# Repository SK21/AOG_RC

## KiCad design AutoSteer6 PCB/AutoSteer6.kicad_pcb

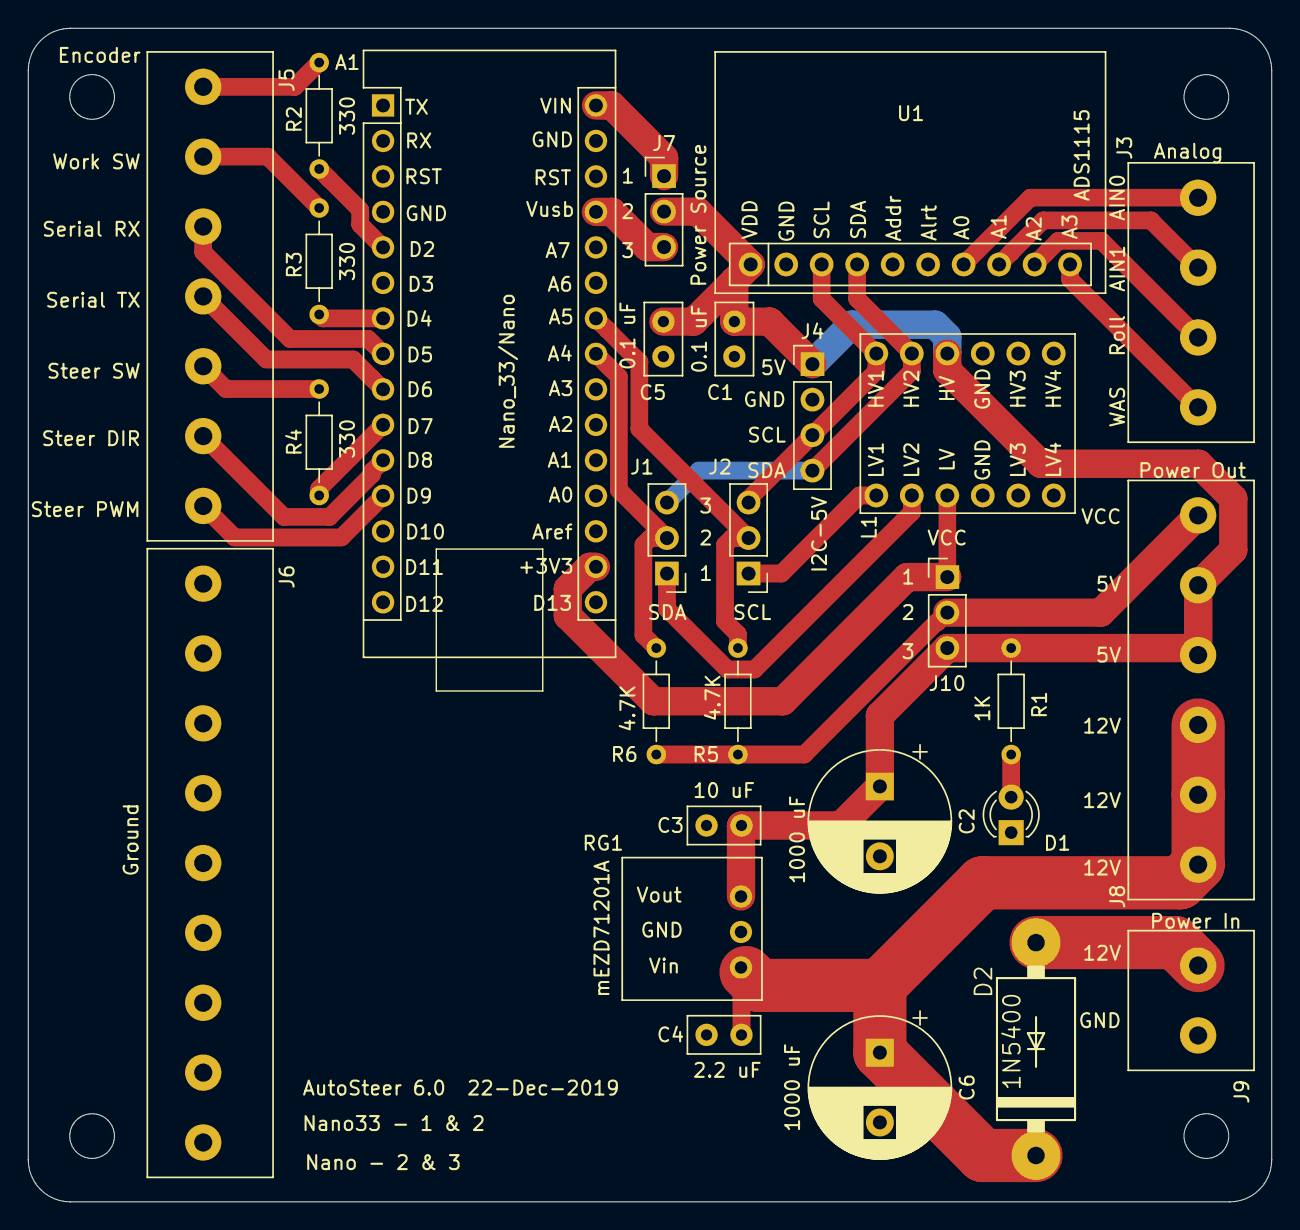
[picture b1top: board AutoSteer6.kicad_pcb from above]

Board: 2 copper layers, 89.0 x 84.0 mm, 28 parts (0 on the bottom side), 29 nets.

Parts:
A1: Nano_33/Nano; Nano_33
C1, C5: 0.1 uF; C_Disc_D5.0mm_W2.5mm_P2.50mm
C2, C6: 1000 uF; CP_Radial_D10.0mm_P5.00mm
C3: 10 uF; C_Disc_D5.0mm_W2.5mm_P2.50mm
C4: 2.2 uF; C_Disc_D5.0mm_W2.5mm_P2.50mm
D1: LED; LED_D3.0mm
D2: 1N5400
J1: SDA; PinHeader_1x03_P2.54mm_Vertical
J2: SCL; PinHeader_1x03_P2.54mm_Vertical
J3: Analog; Phoenix_4_pin_5mm_terminal_block
J4: I2C-5V; PinHeader_1x04_P2.54mm_Vertical
J5: GPIO's; Phoenix_7_pin_5mm_terminal_block
J6: Ground; Phoenix_9_pin_5mm_terminal_block
J7: Power Source; PinHeader_1x03_P2.54mm_Vertical
J8: Power Out; Phoenix_6_pin_5mm_terminal_block
J9: Power In; Phoenix_2_pin_5mm_terminal_block
J10: VCC; PinHeader_1x03_P2.54mm_Vertical
L1: LLC
R1: 1K; R_Axial_DIN0204_L3.6mm_D1.6mm_P7.62mm_Horizontal
R2, R3, R4: 330; R_Axial_DIN0204_L3.6mm_D1.6mm_P7.62mm_Horizontal
R5, R6: 4.7K; R_Axial_DIN0204_L3.6mm_D1.6mm_P7.62mm_Horizontal
RG1: mEZD71201A
U1: ADS1115; ads1115

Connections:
GND: A1.14, A1.19, C1.2, C2.2, C3.2, C4.2, C5.2, C6.2, D1.1, J4.2, J6.1, J6.2, J6.3, J6.4, J6.5, J6.6, J6.7, J6.8, J6.9, J9.1, L1.4, L1.10, RG1.2, U1.2, U1.5
unnamed: A1.2, J10.1, L1.3
unnamed: A1.8, J1.2, R6.2
unnamed: A1.9, J2.2, R5.2
unnamed: A1.12, J7.3
unnamed: A1.15, J7.1
unnamed: A1.20, R2.2
unnamed: A1.22, R3.2
unnamed: A1.23, J5.3
unnamed: A1.24, J5.4
unnamed: A1.25, R4.2
unnamed: A1.26, J5.6
unnamed: A1.27, J5.7
unnamed: C1.1, C2.1, C3.1, C5.1, J4.1, J7.2, J8.4, J8.5, J10.3, L1.9, R1.1, RG1.3, U1.1
unnamed: C4.1, C6.1, D2.C, J8.1, J8.2, J8.3, RG1.1
unnamed: D1.2, R1.2
unnamed: D2.A, J9.2
unnamed: J1.1, L1.2
unnamed: J1.3, J4.4, L1.8, U1.4
unnamed: J2.1, L1.1
unnamed: J2.3, J4.3, L1.7, U1.3
unnamed: J3.1, U1.10
unnamed: J3.2, U1.9
unnamed: J3.3, U1.8
unnamed: J3.4, U1.7
unnamed: J5.1, R2.1
unnamed: J5.2, R3.1
unnamed: J5.5, R4.1
unnamed: J8.6, J10.2, R5.1, R6.1

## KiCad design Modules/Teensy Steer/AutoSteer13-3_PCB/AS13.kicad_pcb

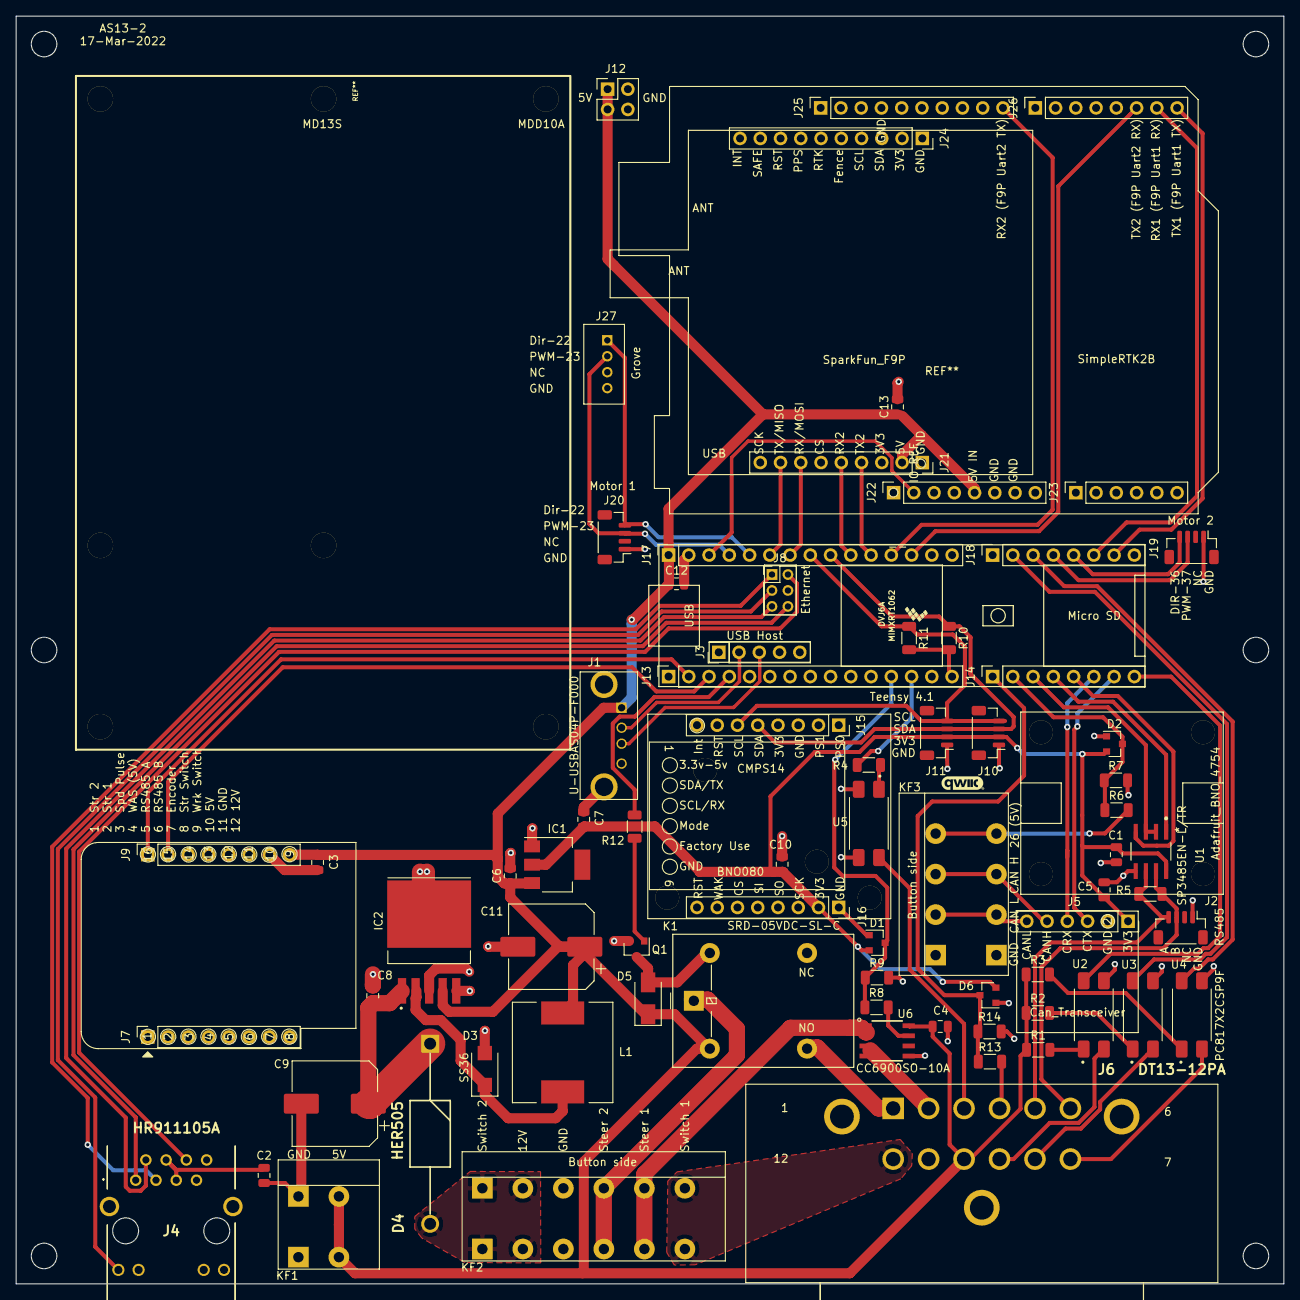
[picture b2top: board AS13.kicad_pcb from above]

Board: 2 copper layers, 159.0 x 159.0 mm, 82 parts (0 on the bottom side), 67 nets.

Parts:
  : MountingHole_3.2mm_M3
  #2,   #3,   #4,   #5,   #6: MountingHole_3.2mm_M3
--: Teensy 4.1; Teensy41_no_pins
C1, C2, C3, C4, C5, C10, C12, C13: 0.1uF; C_0805_2012Metric
C6: 10uF; C_0805_2012Metric
C7: 22uF; C_0805_2012Metric
C8: 1uF; C_0805_2012Metric
C9: 470uF; CP_Elec_10x10.5
C11: 330uF; CP_Elec_10x10.5
D1, D2, D6: BAV99; SOT-23
D3: SS36; SMA(DO-214AC)
D4: HER505; 1N5408
D5: 1N4007; D_SMA
IC1: AZ1117; SOT-223
IC2: XL2596; TO263-5L
J1: U-USBAS04P-F000
J2: RS485; Qwic_vertical
J3: Teensy_USBhost; PinHeader_1x05_P2.54mm_Vertical
J4: HR911105A
J5: PM254V-11-06-H85; PinSocket_1x06_P2.54mm_Vertical
J6: DT13-12PA; DT1312PA
J7: WemosD1_left; PinSocket_1x08_P2.54mm_Vertical
J8: Teensy_Ethernet; PinHeader_2x03_P2.00mm_Vertical
J9: WemosD1_right; PinSocket_1x08_P2.54mm_Vertical
J10, J11: I2C-3V3; Qwic_vertical
J12: Conn_02x02_Counter_Clockwise; PinSocket_2x02_P2.54mm_Vertical
J13, J17: Conn_01x15_Female; PinSocket_1x15_P2.54mm_Vertical
J14, J18: Conn_01x08_Female; PinSocket_1x08_P2.54mm_Vertical
J15: BNO080_left; PinSocket_1x08_P2.54mm_Vertical
J16: BNO080_right; PinSocket_1x08_P2.54mm_Vertical
J19: Motor 2; Qwic_vertical
J20: Motor 1; Qwic_vertical
J21: SF_F9P_left; PinSocket_1x09_P2.54mm_Vertical
J22: ArduSimple_tl; PinSocket_1x08_P2.54mm_Vertical
J23: ArduSimple_bl; PinSocket_1x06_P2.54mm_Vertical
J24: SF_F9P_right; PinSocket_1x10_P2.54mm_Vertical
J25: ArduSimple_tr; PinSocket_1x10_P2.54mm_Vertical
J26: ArduSimple_br; PinSocket_1x08_P2.54mm_Vertical
J27: Grove
K1: SRD-05VDC-SL-C; Songle_SRD-05VDC-SL-C
KF1: KF142V-5.0-2P; KF142V-5.08-2P
KF2: KF142V-5.0-6P; KF142V-5.08-6P
KF3: KF142V-5.0-4P; KF142V-5.08-4P
L1: SMDRI127-330MT; TMPA1265SP-101MN-D
M1: CMPS14; CMPS14_no_pins
Q1: BC847; SOT-23
R1, R2, R3: 200; R_1206_3216Metric
R4: 100; R_1206_3216Metric
R5: 120; R_1206_3216Metric
R6, R8, R12, R13: 1K; R_1206_3216Metric
R7, R9, R14: 2K; R_1206_3216Metric
R10, R11: 2.2K; R_1206_3216Metric
U1: SP3485EN-L/TR; Maxim_Integrated-S8-2-0-P-MFG
U2, U3, U4, U5: PC817X2CSP9F; SOIC254P960X420-4N
U6: CC6900SO-10A; SOIC127P600X175-8N

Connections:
GND: C1.2, C2.2, C3.2, C4.2, C5.2, C6.2, C7.2, C8.2, C9.2, C10.2, C11.2, C12.2, C13.2, D1.1, D2.1, D3.2, D6.1, IC1.1, IC2.3, IC2.5, IC2.6, J1.4, J1.5, J1.6, J2.1, J3.4, J3.5, J4.8, J4.10, J4.MH1, J4.MH2, J5.2, J6.11, J8.4, J9.7, J10.1, J11.1, J12.3, J12.4, J13.1, J16.1, J17.2, J17.15, J19.1, J20.1, J21.1, J22.6, J22.7, J25.4, J27.4, KF1.1, KF2.3, KF3.1, Q1.2, R7.2, R9.2, R14.2, U1.5, U2.3, U3.3, U4.3, U5.2, U5.3, U6.5
unnamed: C1.1, C5.1, C7.1, C10.1, D1.2, D2.2, D6.2, IC1.2, J5.1, J10.2, J11.2, J16.2, U1.8
unnamed: C2.1, J4.4, J4.5
unnamed: C8.1, C9.1, D4.1, IC2.1
unnamed: C3.1, C4.1, C6.1, C11.1, C12.1, C13.1, D5.1, IC1.3, IC2.4, J1.1, J6.10, J9.8, J12.1, J12.2, J17.1, J21.2, J22.5, K1.1, KF1.2, L1.2, R1.1, R2.1, R3.1, U6.8
unnamed: D1.3, J13.12, R8.1, R9.1
unnamed: D2.3, J14.2, R6.1, R7.1
unnamed: D3.1, IC2.2, L1.1
unnamed: D4.2, KF2.1, KF2.2
unnamed: D5.2, K1.2, Q1.3
unnamed: D6.3, J14.1, R13.1, R14.1
unnamed: J1.2, J3.2
unnamed: J1.3, J3.3
unnamed: J2.3, J6.6, R5.1, U1.7
unnamed: J2.4, J6.5, R5.2, U1.6
unnamed: J4.1, J8.6
unnamed: J4.2, J8.5
unnamed: J4.3, J8.1
unnamed: J4.6, J8.2
unnamed: J4.9, J8.3
unnamed: J5.5, KF3.3
unnamed: J5.6, KF3.2
unnamed: J6.1, K1.5
unnamed: J6.2, U6.3, U6.4
unnamed: J6.3, U5.4
unnamed: J6.4, R13.2
unnamed: J6.7, U4.2
unnamed: J6.8, U3.2
unnamed: J6.9, U2.2
unnamed: J6.12, KF2.6
unnamed: J10.3, J11.3, J15.5, J17.9, R10.1
unnamed: J10.4, J11.4, J15.6, J17.8, R11.1
unnamed: J9.1, J13.2
unnamed: J9.2, J13.3
unnamed: J13.4, R12.2
unnamed: J13.13, R4.1
unnamed: J13.15, R10.2, R11.2
unnamed: J14.3, U1.2, U1.3
unnamed: J14.4, U1.1
unnamed: J14.5, U1.4
unnamed: J5.4, J14.6
unnamed: J5.3, J14.7
unnamed: J14.8, U2.4
unnamed: J17.3, J22.2
unnamed: J17.4, J20.3, J27.2
unnamed: J17.5, J20.4, J27.1
unnamed: J17.6, J21.8
unnamed: J17.7, J21.7
unnamed: J17.10, J21.5
unnamed: J17.11, J21.4
unnamed: J17.12, J25.10
unnamed: J17.13, J26.6
unnamed: J18.2, U3.4
unnamed: J18.3, U4.4
unnamed: J18.4, J19.3
unnamed: J18.5, J19.4
unnamed: J18.6, J26.7
unnamed: J18.7, J26.8
unnamed: K1.3, KF2.4
unnamed: KF2.5, U6.1, U6.2
unnamed: KF3.4, R6.2
unnamed: Q1.1, R12.1
unnamed: R1.2, U2.1
unnamed: R2.2, U3.1
unnamed: R3.2, U4.1
unnamed: R4.2, U5.1
unnamed: R8.2, U6.7

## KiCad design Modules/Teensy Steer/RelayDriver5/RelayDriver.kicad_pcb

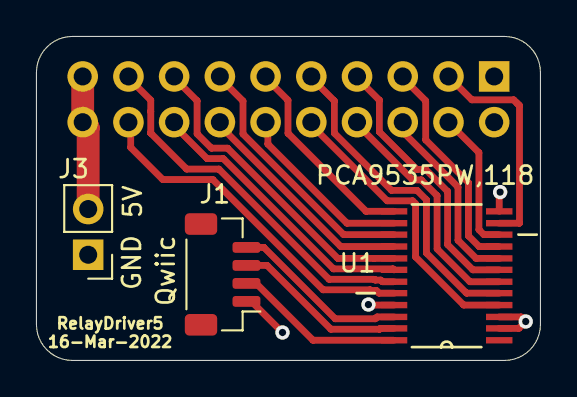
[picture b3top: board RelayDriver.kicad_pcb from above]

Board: 2 copper layers, 28.0 x 18.0 mm, 4 parts (1 on the bottom side), 21 nets.

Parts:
J1: Qwiic; Qwic_vertical
J2: PinSocket_2x10_P2.54mm_Vertical
J3: PinHeader_1x02_P2.54mm_Vertical
U1: PCA9535PW,118; SOP65P640X110-24N

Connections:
GND: J1.1, J2.1, J2.2, J3.1, U1.2, U1.3, U1.12, U1.21
unnamed: J1.2, U1.24
unnamed: J1.3, U1.23
unnamed: J1.4, U1.22
unnamed: J2.3, U1.11
unnamed: J2.4, U1.10
unnamed: J2.5, U1.9
unnamed: J2.6, U1.8
unnamed: J2.7, U1.7
unnamed: J2.8, U1.6
unnamed: J2.9, U1.5
unnamed: J2.10, U1.4
unnamed: J2.11, U1.13
unnamed: J2.12, U1.14
unnamed: J2.13, U1.15
unnamed: J2.14, U1.16
unnamed: J2.15, U1.17
unnamed: J2.16, U1.18
unnamed: J2.17, U1.19
unnamed: J2.18, U1.20
unnamed: J2.19, J2.20, J3.2

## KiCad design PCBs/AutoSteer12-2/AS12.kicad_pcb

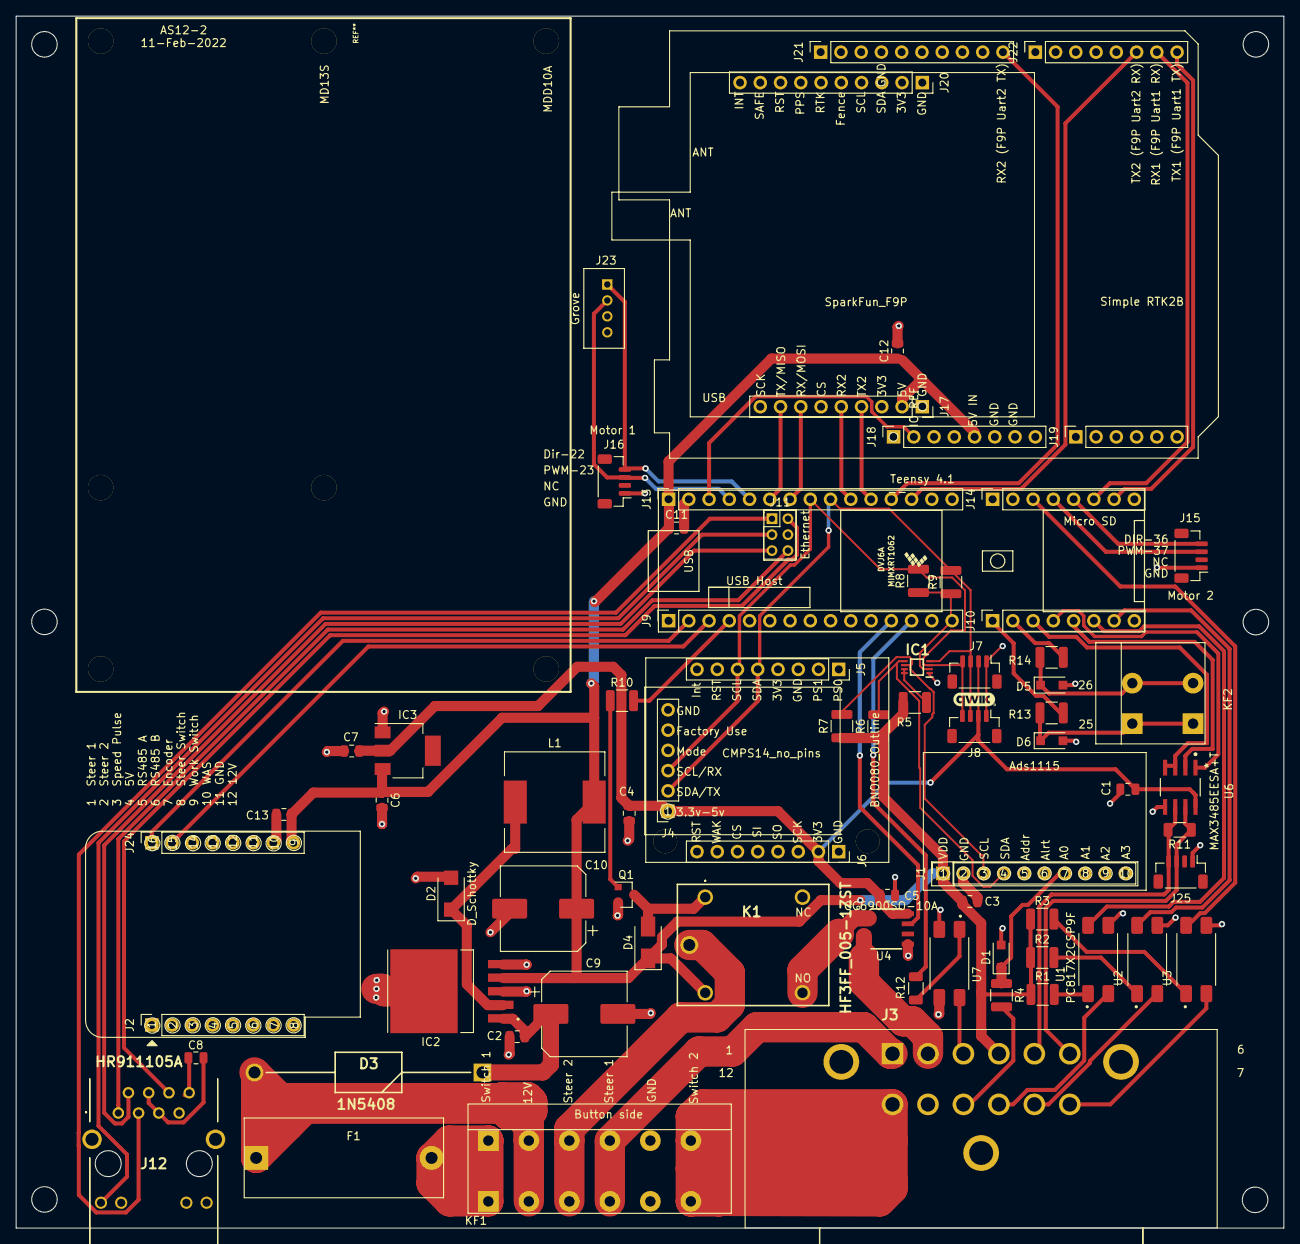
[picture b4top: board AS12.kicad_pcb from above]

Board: 2 copper layers, 159.0 x 152.0 mm, 81 parts (0 on the bottom side), 66 nets.

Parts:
 : MountingHole_3.2mm_M3
 #2,  #3,  #4,  #5,  #6: MountingHole_3.2mm_M3
--: Teensy 4.1; Teensy41_no_pins
C1, C3, C4, C5, C8, C11, C12, C13: 0.1uF; C_0805_2012Metric
C2: CL21B105KAFNNNE; C_0805_2012Metric
C6: 10uF; C_0805_2012Metric
C7: 22uF; C_0805_2012Metric
C9: RVT1V471M1010; CP_Elec_10x10.5
C10: RVT1V331M1010; CP_Elec_10x10.5
D1, D5, D6: Zener Diode; D_SOD-123F
D2: D_Schottky; SMA(DO-214AC)
D3: 1N5408; DO-201AD-28
D4: 1N4007; D_SMA
F1: Fuse; Fuse_Holder_C3131
IC1: PCA9306DCUR; SOP50P310X90-8N
IC2: XL2596; TO263-5L
IC3: AZ1117; SOT-223
J1: ADS1115; PinSocket_1x10_P2.54mm_Vertical
J2: WemosD1_left; PinSocket_1x08_P2.54mm_Vertical
J3: DT13-12PA; DT1312PA
J4: CMPS14; PinSocket_1x06_P2.54mm_Vertical
J5: BNO080_left; PinSocket_1x08_P2.54mm_Vertical
J6: BNO080_right; PinSocket_1x08_P2.54mm_Vertical
J7, J8: I2C-3V3; Qwic_vertical
J9, J13: Conn_01x15_Female; PinSocket_1x15_P2.54mm_Vertical
J10, J14: Conn_01x08_Female; PinSocket_1x08_P2.54mm_Vertical
J11: Teensy_Ethernet; PinHeader_2x03_P2.00mm_Vertical
J12: HR911105A
J15: Motor 2; Qwic_vertical
J16: Motor 1; Qwic_vertical
J17: SF_F9P_left; PinSocket_1x09_P2.54mm_Vertical
J18: ArduSimple_tl; PinSocket_1x08_P2.54mm_Vertical
J19: ArduSimple_bl; PinSocket_1x06_P2.54mm_Vertical
J20: SF_F9P_right; PinSocket_1x10_P2.54mm_Vertical
J21: ArduSimple_tr; PinSocket_1x10_P2.54mm_Vertical
J22: ArduSimple_br; PinSocket_1x08_P2.54mm_Vertical
J23: Grove
J24: WemosD1_right; PinSocket_1x08_P2.54mm_Vertical
J25: RS485; Qwic_vertical
K1: HF3FF_005-1ZST; HF3FF0121ZST
KF1: KF142V-5.0-6P; KF142V-5.08-6P
KF2: KF142V-5.0-2P; KF142V-5.08-2P
L1: SMDRI127-330MT; TMPA1265SP-101MN-D
M1: CMPS14_no_pins
Q1: BC847; SOT-23
R1, R2, R3, R4, R13, R14: 200; R_1210_3225Metric
R5: 200K; R_1210_3225Metric
R6, R7: 341; R_1210_3225Metric
R8, R9: 217; R_1210_3225Metric
R10: 1K; R_1210_3225Metric
R11: 120; R_1206_3216Metric
R12: 100; R_1206_3216Metric
U1, U2, U3, U7: PC817X2CSP9F; SOIC254P960X420-4N
U4: CC6900SO-10A; SOIC127P600X175-8N
U6: MAX3485EESA+T; Maxim_Integrated-S8-2-0-P-MFG

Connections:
GND: C1.2, C2.2, C3.2, C4.2, C5.2, C6.2, C7.2, C8.2, C9.2, C10.2, C11.2, C12.2, C13.2, D1.2, D2.2, D5.2, D6.2, IC1.1, IC2.3, IC2.5, IC2.6, IC3.1, J1.2, J1.5, J3.11, J4.6, J6.1, J7.1, J8.1, J9.1, J11.4, J12.8, J12.10, J13.2, J13.15, J15.1, J16.1, J17.1, J18.6, J18.7, J21.4, J23.4, J24.7, J25.1, KF1.5, Q1.2, U1.3, U2.3, U3.3, U4.5, U6.5, U7.2, U7.3
unnamed: C1.1, C4.1, C5.1, C7.1, IC3.2, J4.1, J6.2, J7.2, J8.2, U4.8, U6.8
unnamed: C2.1, C9.1, D3.1, IC2.1
unnamed: C8.1, J12.4, J12.5
unnamed: C3.1, C6.1, C10.1, C11.1, C12.1, C13.1, D4.1, IC2.4, IC3.3, J1.1, J3.4, J13.1, J17.2, J18.5, J24.8, K1.3, L1.2, R1.1, R2.1, R3.1, R5.1, R6.1, R7.1
unnamed: D1.1, J1.7, R4.1
unnamed: D2.1, IC2.2, L1.1
unnamed: D3.2, F1.1, KF1.2
unnamed: D4.2, K1.1, Q1.3
unnamed: D5.1, KF2.2, R14.1
unnamed: D6.1, KF2.1, R13.1
unnamed: F1.2, KF1.1
unnamed: IC1.2, J9.15, R8.1, R9.1
unnamed: IC1.3, J4.3, J5.6, J7.4, J8.4, J13.8, R8.2
unnamed: IC1.4, J4.2, J5.5, J7.3, J8.3, J13.9, R9.2
unnamed: IC1.5, J1.4, R6.2
unnamed: IC1.6, J1.3, R7.2
unnamed: IC1.7, IC1.8, R5.2
unnamed: J3.1, KF1.4
unnamed: J3.2, U4.3, U4.4
unnamed: J3.3, U7.4
unnamed: J3.7, U3.2
unnamed: J3.8, U2.2
unnamed: J3.9, U1.2
unnamed: J3.10, R4.2
unnamed: J3.12, KF1.6
unnamed: J9.4, R10.2
unnamed: J9.12, U4.7
unnamed: J9.13, R12.1
unnamed: J10.1, R13.2
unnamed: J10.2, R14.2
unnamed: J10.3, U6.3, U6.4
unnamed: J10.4, U6.1
unnamed: J10.5, U6.2
unnamed: J10.6, U1.4
unnamed: J10.7, U2.4
unnamed: J11.1, J12.3
unnamed: J11.2, J12.6
unnamed: J11.3, J12.9
unnamed: J11.5, J12.2
unnamed: J11.6, J12.1
unnamed: J13.3, J18.2
unnamed: J13.4, J16.3, J23.2
unnamed: J13.5, J16.4, J23.1
unnamed: J13.6, J17.8
unnamed: J13.7, J17.7
unnamed: J13.10, J17.5
unnamed: J13.11, J17.4
unnamed: J13.12, J21.10
unnamed: J13.13, J22.6
unnamed: J14.3, U3.4
unnamed: J14.4, J15.3
unnamed: J14.5, J15.4
unnamed: J14.6, J22.7
unnamed: J14.7, J22.8
unnamed: J9.2, J24.1
unnamed: J9.3, J24.2
unnamed: J3.6, J25.3, R11.1, U6.7
unnamed: J3.5, J25.4, R11.2, U6.6
unnamed: K1.2, KF1.3
unnamed: K1.4, U4.1, U4.2
unnamed: Q1.1, R10.1
unnamed: R1.2, U1.1
unnamed: R2.2, U2.1
unnamed: R3.2, U3.1
unnamed: R12.2, U7.1

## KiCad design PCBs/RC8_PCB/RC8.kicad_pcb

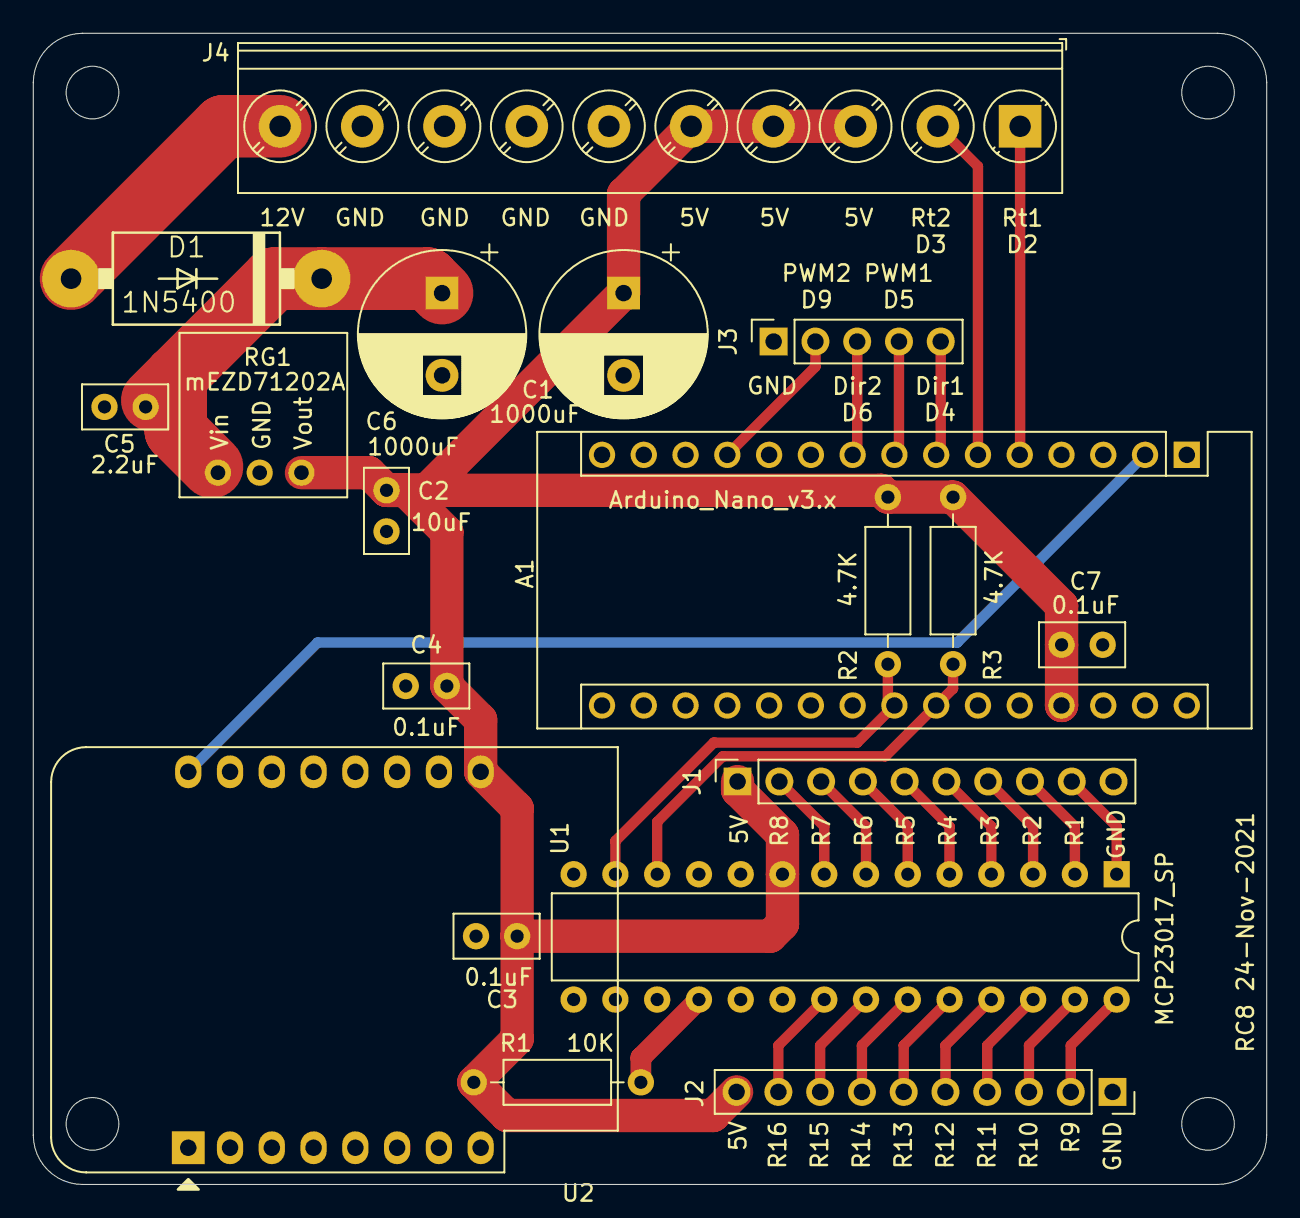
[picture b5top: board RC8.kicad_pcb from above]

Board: 2 copper layers, 75.0 x 70.0 mm, 23 parts (0 on the bottom side), 30 nets.

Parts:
 : MountingHole_3.2mm_M3
 #2,  #3,  #4: MountingHole_3.2mm_M3
A1: Arduino_Nano_v3.x; Arduino_Nano
C1, C6: 1000uF; CP_Radial_D10.0mm_P5.00mm
C2: 10uF; C_Disc_D5.0mm_W2.5mm_P2.50mm
C3, C4, C7: 0.1uF; C_Disc_D5.0mm_W2.5mm_P2.50mm
C5: 2.2uF; C_Disc_D5.0mm_W2.5mm_P2.50mm
D1: 1N5400
J1, J2: Conn_01x10_Female; PinSocket_1x10_P2.54mm_Vertical
J3: Motor Control; PinSocket_1x05_P2.54mm_Vertical
J4: Screw_Terminal_01x10; TerminalBlock_Phoenix_PT-1,5-10-5.0-H_1x10_P5.00mm_Horizont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
R1: 10K; R_Axial_DIN0207_L6.3mm_D2.5mm_P10.16mm_Horizontal
R2, R3: 4.7K; R_Axial_DIN0207_L6.3mm_D2.5mm_P10.16mm_Horizontal
RG1: mEZD71202A
U1: MCP23017_SP; DIP-28_W7.62mm
U2: WeMos_D1_mini; WEMOS_D1_mini_light

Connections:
GND: A1.4, A1.29, C1.2, C2.2, C3.1, C4.1, C5.2, C6.2, C7.1, J1.10, J2.1, J3.1, J4.6, J4.7, J4.8, J4.9, RG1.2, U1.10, U1.15, U1.16, U1.17, U2.10
unnamed: A1.2, U2.16
unnamed: A1.5, J4.1
unnamed: A1.6, J4.2
unnamed: A1.7, J3.5
unnamed: A1.8, J3.4
unnamed: A1.9, J3.3
unnamed: A1.12, J3.2
unnamed: A1.23, R2.2, U1.13
unnamed: A1.24, R3.2, U1.12
unnamed: A1.27, C1.1, C2.1, C3.2, C4.2, C7.2, J1.1, J2.10, J4.3, J4.4, J4.5, R1.1, R2.1, R3.1, RG1.3, U1.9, U2.9
unnamed: C5.1, C6.1, D1.C, RG1.1
unnamed: D1.A, J4.10
unnamed: J1.2, U1.8
unnamed: J1.3, U1.7
unnamed: J1.4, U1.6
unnamed: J1.5, U1.5
unnamed: J1.6, U1.4
unnamed: J1.7, U1.3
unnamed: J1.8, U1.2
unnamed: J1.9, U1.1
unnamed: J2.2, U1.28
unnamed: J2.3, U1.27
unnamed: J2.4, U1.26
unnamed: J2.5, U1.25
unnamed: J2.6, U1.24
unnamed: J2.7, U1.23
unnamed: J2.8, U1.22
unnamed: J2.9, U1.21
unnamed: R1.2, U1.18

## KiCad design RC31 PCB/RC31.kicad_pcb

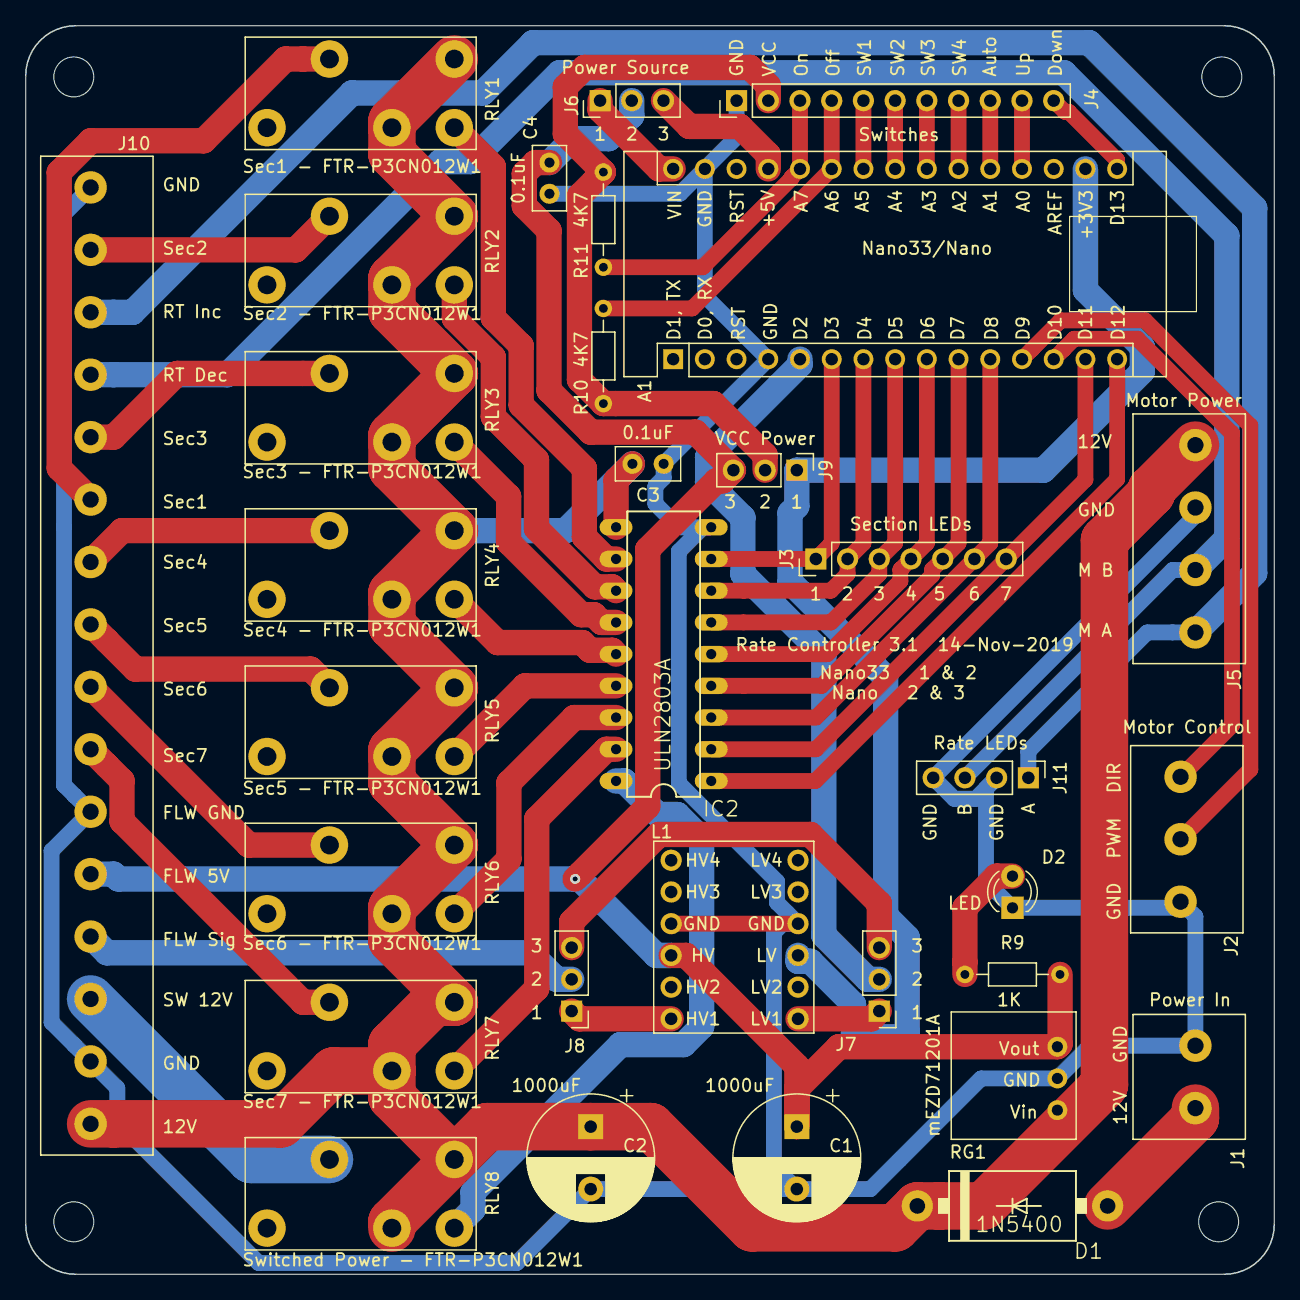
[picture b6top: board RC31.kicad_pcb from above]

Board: 2 copper layers, 100.0 x 100.0 mm, 36 parts (0 on the bottom side), 51 nets.

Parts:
A1: Nano33/Nano; Arduino_Nano
C1, C2: 1000uF; CP_Radial_D10.0mm_P5.00mm
C3, C4: 0.1uF; C_Disc_D5.0mm_W2.5mm_P2.50mm
D1: 1N5400
D2: LED; LED_D3.0mm
H1, H2, H3, H4: MountingHole; MountingHole_3.2mm_M3
IC2: ULN2803A; DIL18
J1: Power In; Phoenix_2_pin_5mm_terminal_block
J2: Motor Control; Phoenix_3_pin_5mm_terminal_block
J3: Section LEDs; PinHeader_1x07_P2.54mm_Vertical
J4: Switches; PinHeader_1x11_P2.54mm_Vertical
J5: Motor Power; Phoenix_4_pin_5mm_terminal_block
J6: Power Source; PinHeader_1x03_P2.54mm_Vertical
J7: Flow Selection2; PinHeader_1x03_P2.54mm_Vertical
J8: Flow Selection1; PinHeader_1x03_P2.54mm_Vertical
J9: VCC Power; PinHeader_1x03_P2.54mm_Vertical
J10: Screw_Terminal_01x16; Phoenix_16_pin_5mm_terminal_block
J11: Rate LEDs; PinHeader_1x04_P2.54mm_Vertical
L1: LLC
R9: 1K; R_Axial_DIN0204_L3.6mm_D1.6mm_P7.62mm_Horizontal
R10, R11: 4K7; R_Axial_DIN0204_L3.6mm_D1.6mm_P7.62mm_Horizontal
RG1: mEZD71201A
RLY1: Sec1 - FTR-P3CN012W1; FTR-P3_Relay
RLY2: Sec2 - FTR-P3CN012W1; FTR-P3_Relay
RLY3: Sec3 - FTR-P3CN012W1; FTR-P3_Relay
RLY4: Sec4 - FTR-P3CN012W1; FTR-P3_Relay
RLY5: Sec5 - FTR-P3CN012W1; FTR-P3_Relay
RLY6: Sec6 - FTR-P3CN012W1; FTR-P3_Relay
RLY7: Sec7 - FTR-P3CN012W1; FTR-P3_Relay
RLY8: Switched Power - FTR-P3CN012W1; FTR-P3_Relay

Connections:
GND: A1.4, A1.29, C1.2, C2.2, C3.1, C4.2, D2.1, IC2.9, J1.2, J2.3, J4.1, J5.3, J10.1, J10.11, J10.15, J11.2, J11.4, L1.4, L1.10, RG1.2
unnamed: A1.5, J7.2
unnamed: A1.6, IC2.8, J3.1
unnamed: A1.7, IC2.7, J3.2
unnamed: A1.8, IC2.6, J3.3
unnamed: A1.9, IC2.5, J3.4
unnamed: A1.10, IC2.4, J3.5
unnamed: A1.11, IC2.3, J3.6
unnamed: A1.12, J2.2
unnamed: A1.13, J2.1
unnamed: A1.14, IC2.2, J3.7
unnamed: A1.15, IC2.1
unnamed: A1.16, J4.11
unnamed: A1.17, J9.1, L1.3
unnamed: A1.19, J4.10
unnamed: A1.20, J4.9
unnamed: A1.21, J4.8
unnamed: A1.22, J4.7
unnamed: A1.23, J4.6
unnamed: A1.24, J4.5
unnamed: A1.25, J4.4, R10.2
unnamed: A1.26, J4.3, R11.2
unnamed: A1.27, J6.3
unnamed: A1.30, J6.1
unnamed: C1.1, C4.1, J6.2, J9.3, J10.12, L1.9, R9.1, RG1.3
unnamed: C2.1, C3.2, D1.C, IC2.10, J5.4, J10.16, RG1.1, RLY1.1, RLY1.4, RLY2.1, RLY2.4, RLY3.1, RLY3.4, RLY4.1, RLY4.4, RLY5.1, RLY5.4, RLY6.1, RLY6.4, RLY7.1, RLY7.4, RLY8.1, RLY8.4
unnamed: D1.A, J1.1
unnamed: D2.2, R9.2
unnamed: IC2.11, RLY1.5
unnamed: IC2.12, RLY2.5
unnamed: IC2.13, RLY3.5
unnamed: IC2.14, RLY4.5
unnamed: IC2.15, RLY5.5
unnamed: IC2.16, RLY6.5
unnamed: IC2.17, RLY7.5
unnamed: IC2.18, RLY8.5
unnamed: J4.2, J9.2, R10.1, R11.1
unnamed: J7.1, L1.1
unnamed: J7.3, J8.3
unnamed: J8.1, L1.7
unnamed: J10.2, RLY2.2
unnamed: J5.1, J10.3, J11.1
unnamed: J5.2, J10.4, J11.3
unnamed: J10.5, RLY3.2
unnamed: J10.6, RLY1.2
unnamed: J10.7, RLY4.2
unnamed: J10.8, RLY5.2
unnamed: J10.9, RLY6.2
unnamed: J10.10, RLY7.2
unnamed: J8.2, J10.13
unnamed: J10.14, RLY8.2

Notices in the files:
parts and their libraries:
Copyright 2021 Accelerated Designs. All rights reserved.
